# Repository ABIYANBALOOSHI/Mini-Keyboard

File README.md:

# 5-Key Macro Keyboard

A custom-designed 5-key mechanical macro keypad powered by a Seeeduino XIAO RP2040, built for the Hack Club Forge submission.

## Overview
This project is a compact, programmable 5-key macro pad designed from scratch using KiCad. It features 5 Cherry MX mechanical switches, a custom diode matrix using SOD-323 diodes, and a Seeeduino XIAO RP2040 microcontroller mounted via a 7-pin header.

## Features
* **Microcontroller**: Seeeduino XIAO RP2040 for high performance and easy programmability.
* **Switches**: 5x Cherry MX mechanical switches with custom routing.
* **Protection**: SOD-323 diodes to prevent ghosting and ensure precise input registration.
* **Design**: Fully designed, routed, and DRC-verified in KiCad.

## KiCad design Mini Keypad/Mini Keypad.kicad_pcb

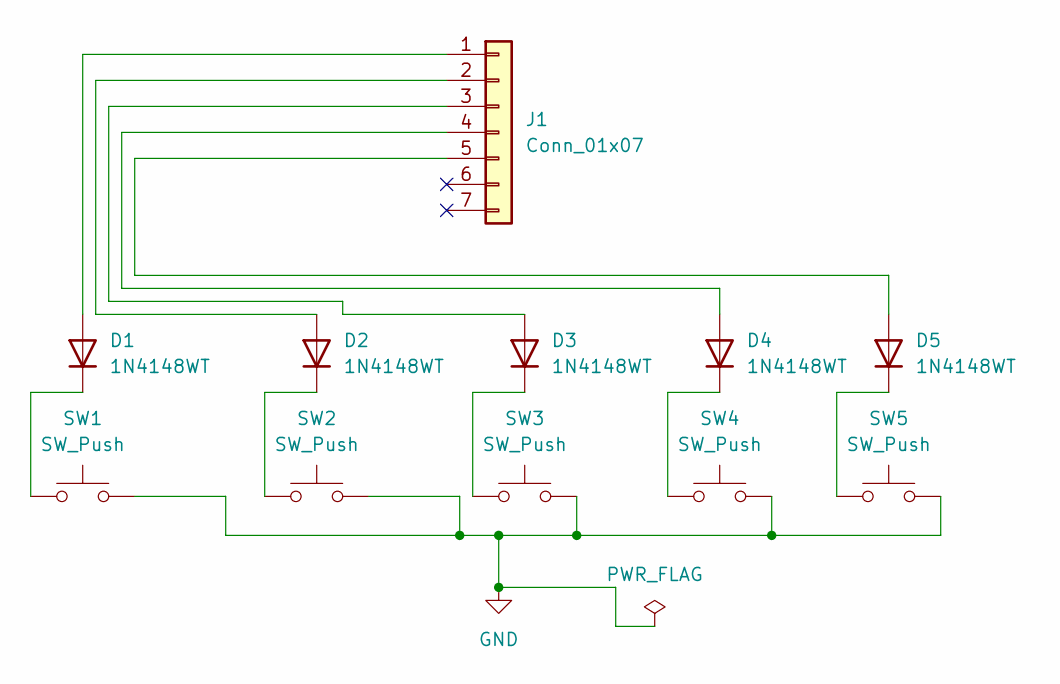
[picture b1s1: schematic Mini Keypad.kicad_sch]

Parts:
D1, D2, D3, D4, D5: 1N4148WT; D_SOD-323
J1: Conn_01x07; PinHeader_1x07_P2.54mm_Vertical
SW1, SW2, SW3, SW4, SW5: SW_Push; SW_Cherry_MX_1.00u_PCB

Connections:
GND: SW1.2, SW2.2, SW3.2, SW4.2, SW5.2
unnamed: D1.2 (A), J1.1
unnamed: D1.1 (K), SW1.1
unnamed: D2.2 (A), J1.2
unnamed: D2.1 (K), SW2.1
unnamed: D3.2 (A), J1.3
unnamed: D3.1 (K), SW3.1
unnamed: D4.2 (A), J1.4
unnamed: D4.1 (K), SW4.1
unnamed: D5.2 (A), J1.5
unnamed: D5.1 (K), SW5.1

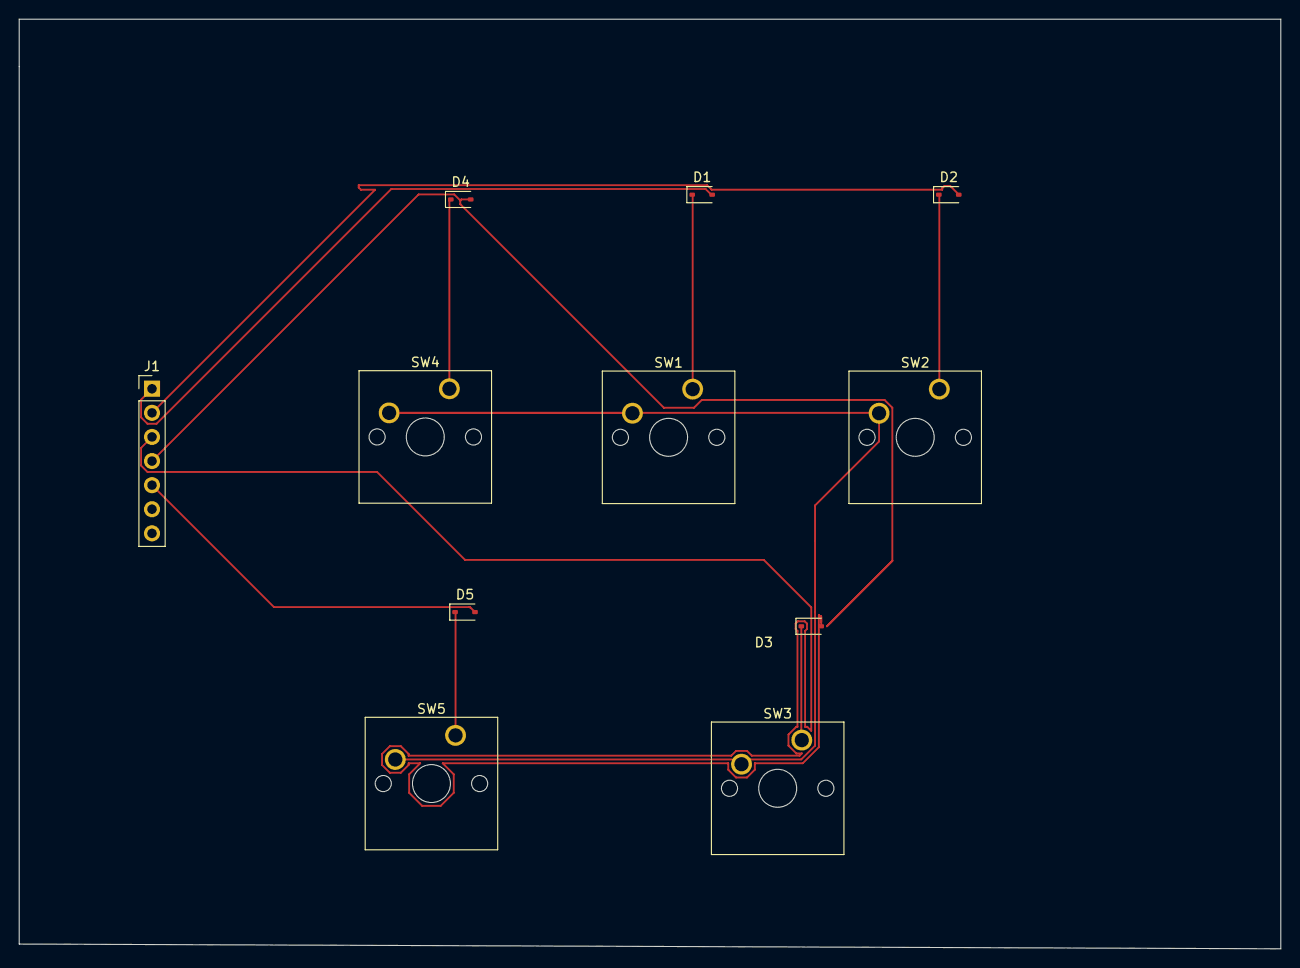
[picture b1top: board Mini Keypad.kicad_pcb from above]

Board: 2 copper layers, 133.0 x 98.0 mm, 11 parts (0 on the bottom side), 11 nets.
